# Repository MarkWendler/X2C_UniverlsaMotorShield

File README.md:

# X2C_Motorshield
Universal motor driver board for X2C Development board

## Planned Main features
* BLDC, PMSM motor drive
* 2 Phase Current sense
* 3 Phase voltage sense
* Led feedback from PWM outputs                                                                   
* Over current protection
* Optional Motor supply (Up to 48V Not)
* Interface to HALL sensor and Quadrature Encoder
* DC common current sens
* External OPAMP
* CAN Bus

## Recommended parts
* MOSFET:	DMT4002LPS			http://www.diodes.com/_files/datasheets/DMT4002LPS.pdf						
* Mosfet Driver:	MIC4607			http://www.microchip.com/wwwproducts/en/MIC4607						
* Current and voltage sense:	MCP6024 http://www.microchip.com/wwwproducts/en/MCP6024						
* 5V Supply LDO:	MCP1790/91									
* 8-12V LDO:	MIC5233 (Adjustable)			http://ww1.microchip.com/downloads/en/DeviceDoc/mic5233.pdf						
* CAN transciever:	ATA6563

### Pinout
Coming soon

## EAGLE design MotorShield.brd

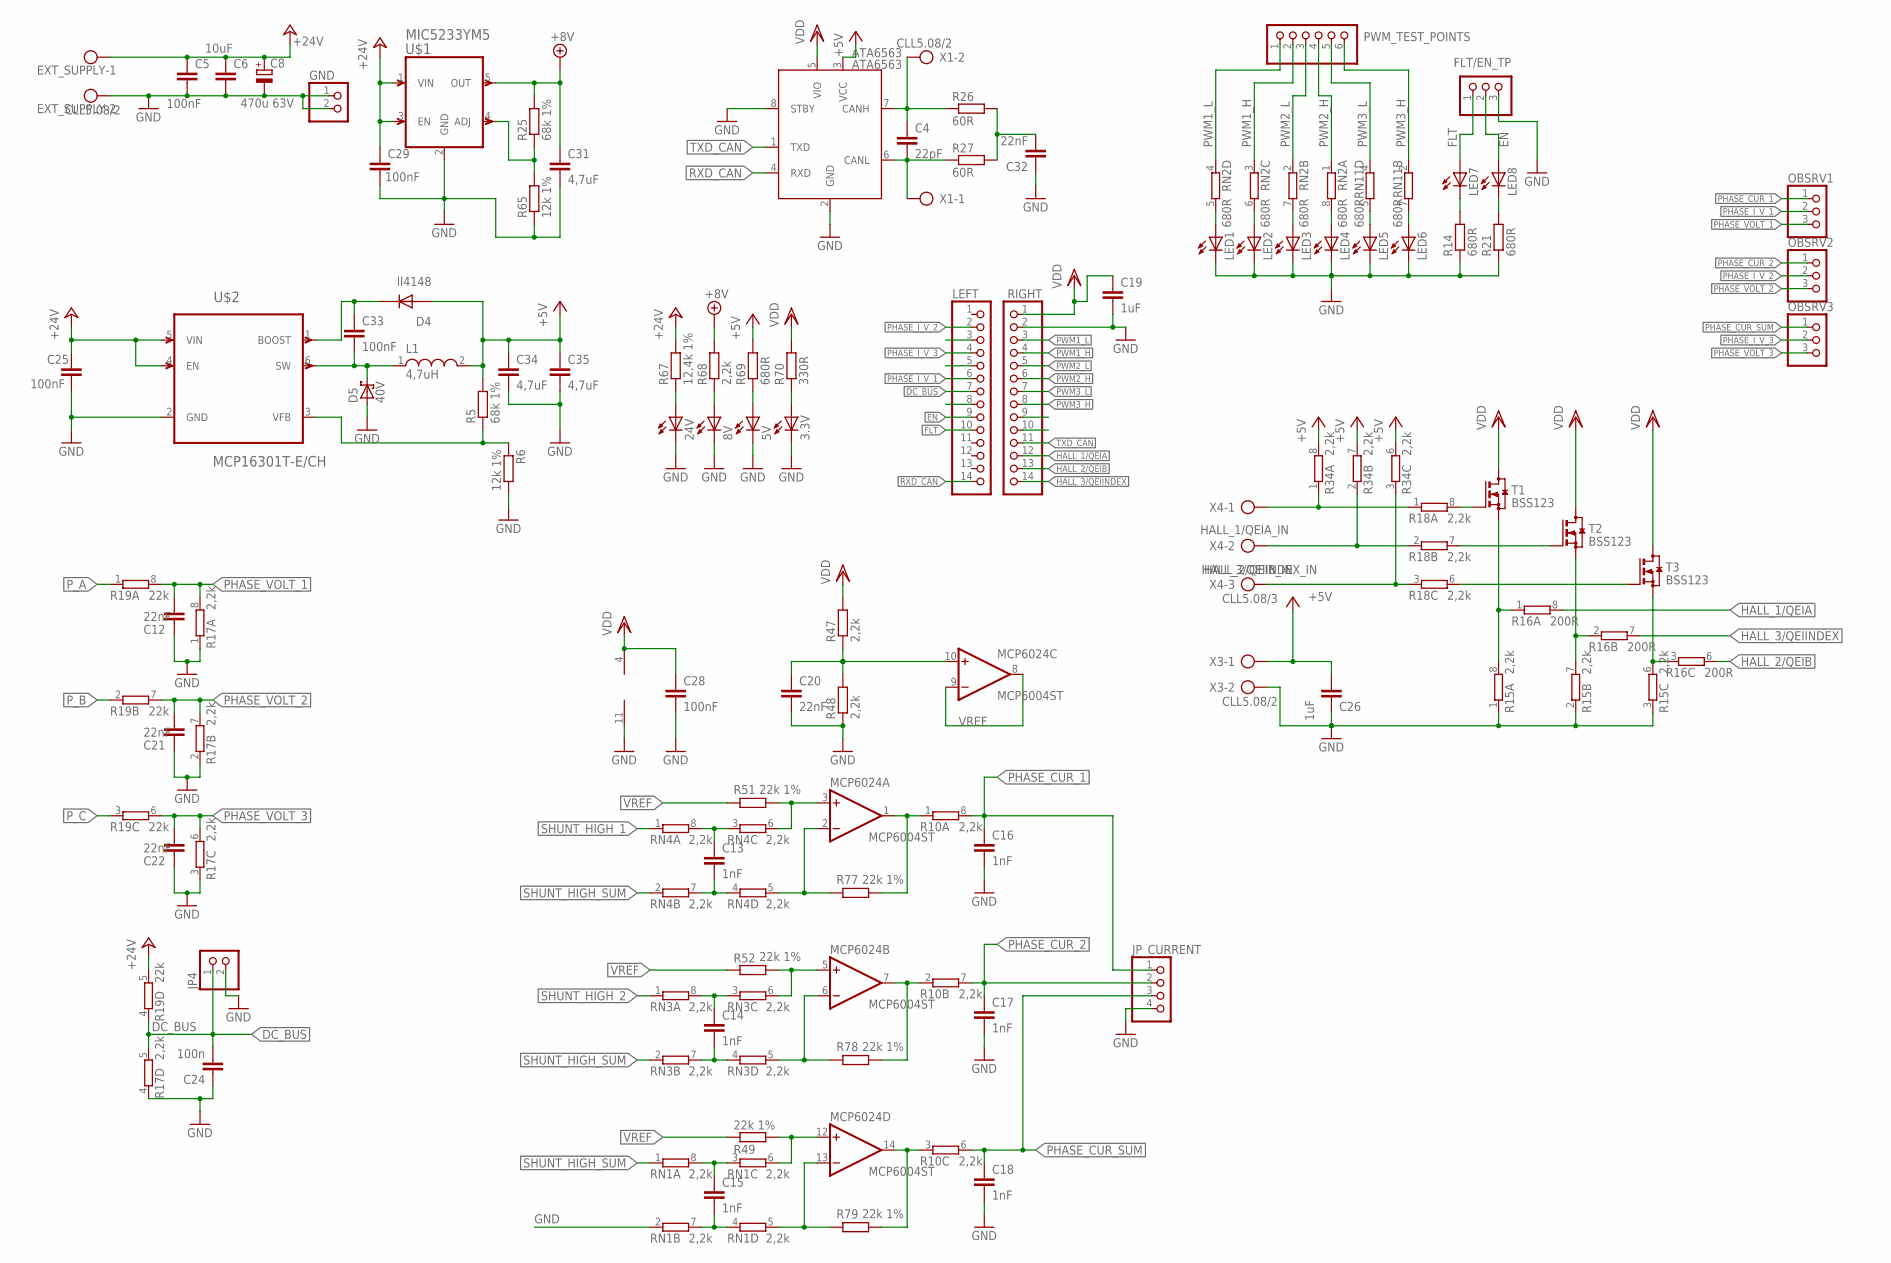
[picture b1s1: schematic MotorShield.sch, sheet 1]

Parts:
3.3V, 5V, 8V, 24V: Green; CHIPLED_0805
ATA6563: ATA6563; SOIC-8
C4: 22pF; C0603K
C5, C25, C28, C29, C33: 100nF; C0603K
C6: 10uF; C1206
C8: 470u 63V; PANASONIC_E
C12, C20, C21, C22, C32: 22nF; C0603K
C13, C14, C15, C16, C17, C18: 1nF; C0603K
C19, C26: 1uF; C0603K
C24: 100n; C0805
C31, C34, C35: 4,7uF; C0603K
D4: ll4148; MINIMELF
D5: 40V; MINIMELF
EXT_SUPPLY: CLL5.08/2
FLT/EN_TP: PINHD-1X3; 1X03
GND: PINHD-1X2; 1X02
JP4: PINHD-1X2; 1X02
JP_CURRENT: PINHD-1X4; 1X04
L1: 4,7uH; WE-TPC_3816
LED1, LED2, LED3, LED4, LED5, LED6: Yellow; CHIPLED_0805
LED7, LED8: Red; CHIPLED_0805
LEFT: PINHD-1X14; 1X14
MCP6024: MCP6004ST; TSSOP14
OBSRV1, OBSRV2, OBSRV3: PINHD-1X3; 1X03
PWM_TEST_POINTS: PINHD-1X6; 1X06
R5, R25: 68k 1%; R0603
R6, R65: 12k 1%; R0603
R10, R15, R17, R18, R34: 2,2k; EXBV8V_A
R14, R21, R69: 680R; R0603
R16: 200R; EXBV8V_A
R19: 22k; EXBV8V_A
R26, R27: 60R; R1206
R47, R48, R68: 2,2k; R0603
R49, R51, R52, R77, R78, R79: 22k 1%; R0603
R67: 12,4k 1%; R0603
R70: 330R; R0603
RIGHT: PINHD-1X14; 1X14
RN1, RN3, RN4: 2,2k; EXBV8V_A
RN2, RN11: 680R; EXBV8V_A
T1, T2, T3: BSS123; SOT23
U$1: MIC5233YM5; TSOT23-5
U$2: MCP16301T-E/CH; SOT23-6
X1, X3: CLL5.08/2
X4: CLL5.08/3

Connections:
+5V: ATA6563.3 (VCC), C26.1, C34.1, C35.1, D4.A, L1.2, R5.2, R34.6 (2), R34.7 (2), R34.8 (2), R69.2, X3.1
+8V: C31.1, R25.2, R68.2, U$1.5 (OUT); also elsewhere on the board
+24V: C5.1, C6.1, C8.+, C25.1, C29.1, EXT_SUPPLY.1, R19.5 (2), R67.2, U$1.1 (VIN), U$1.3 (EN), U$2.4 (EN), U$2.5 (VIN); also elsewhere on the board
CAN_H: ATA6563.7 (CANH), C4.1, R26.1, X1.2
CAN_L: ATA6563.6 (CANL), C4.2, R27.1, X1.1
DC_BUS: C24.2, JP4.1, LEFT.7, R17.5 (2), R19.4 (1)
EN: FLT/EN_TP.2, LED8.A, LEFT.9; also elsewhere on the board
FLT: FLT/EN_TP.1, LED7.A, LEFT.10; also elsewhere on the board
GND: 3.3V.C, 5V.C, 8V.C, 24V.C, ATA6563.2 (GND), ATA6563.8 (STBY), C5.2, C6.2, C8.-, C12.2, C16.2, C17.2, C18.2, C19.2, C20.2, C21.2, C22.2, C24.1, C25.2, C26.2, C28.2, C29.2, C31.2, C32.1, C34.2, C35.2, D5.A, EXT_SUPPLY.2, FLT/EN_TP.3, GND.1, GND.2, JP4.2, JP_CURRENT.4, LED1.C, LED2.C, LED3.C, LED4.C, LED5.C, LED6.C, MCP6024.11 (V-), R6.2, R14.1, R15.1, R15.2 (1), R15.3 (1), R17.1, R17.2 (1), R17.3 (1), R17.4 (1), R21.1, R48.1, R65.1, RIGHT.2, RN1.2 (1), U$1.2 (GND), U$2.2 (GND), X3.2; also elsewhere on the board
HALL_1/QEIA: R16.8 (2), RIGHT.12
HALL_1/QEIA_IN: R18.1, R34.1, X4.1
HALL_2/QEIB: R16.6 (2), RIGHT.13
HALL_2/QEIB_IN: R18.3 (1), R34.3 (1), X4.3
HALL_3/QEIINDEX: R16.7 (2), RIGHT.14
HALL_3/QEIINDEX_IN: R18.2 (1), R34.2 (1), X4.2
unnamed: MCP6024.3 (+IN), R51.2, RN4.6 (2)
unnamed: MCP6024.14 (OUT), R10.3 (1), R79.2
unnamed: MCP6024.7 (OUT), R10.2 (1), R78.2
unnamed: LED8.C, R21.2
unnamed: LED7.C, R14.2
unnamed: MCP6024.5 (+IN), R52.2, RN3.6 (2)
unnamed: C33.2, D5.C, L1.1, U$2.6 (SW)
unnamed: R25.1, R65.2, U$1.4 (ADJ)
unnamed: MCP6024.12 (+IN), R49.2, RN1.6 (2)
unnamed: R15.6 (2), R16.3 (1), T3.2 (S)
unnamed: R15.7 (2), R16.2 (1), T2.2 (S)
unnamed: R15.8 (2), R16.1, T1.2 (S)
unnamed: R18.8 (2), T1.1 (G)
unnamed: R18.7 (2), T2.1 (G)
unnamed: R18.6 (2), T3.1 (G)
unnamed: LED4.A, RN2.8 (2)
unnamed: LED3.A, RN2.7 (2)
unnamed: LED2.A, RN2.6 (2)
unnamed: 24V.A, R67.1
unnamed: 8V.A, R68.1
unnamed: 5V.A, R69.1
unnamed: 3.3V.A, R70.1
unnamed: C13.2, RN4.4 (1), RN4.7 (2)
unnamed: C13.1, RN4.3 (1), RN4.8 (2)
unnamed: MCP6024.2 (-IN), R77.1, RN4.5 (2)
unnamed: LED1.A, RN2.5 (2)
unnamed: C14.2, RN3.4 (1), RN3.7 (2)
unnamed: C14.1, RN3.3 (1), RN3.8 (2)
unnamed: LED5.A, RN11.5 (2)
unnamed: LED6.A, RN11.7 (2)
unnamed: R5.1, R6.1, U$2.3 (VFB)
unnamed: MCP6024.6 (-IN), R78.1, RN3.5 (2)
unnamed: C15.2, RN1.4 (1), RN1.7 (2)
unnamed: C15.1, RN1.3 (1), RN1.8 (2)
unnamed: MCP6024.13 (-IN), R79.1, RN1.5 (2)
unnamed: C33.1, D4.C, U$2.1 (BOOST)
unnamed: C32.2, R26.2, R27.2
unnamed: MCP6024.1 (OUT), R10.1, R77.2
unnamed: C20.1, MCP6024.10 (+IN), R47.1, R48.2
PHASE_CUR_1: C16.1, JP_CURRENT.1, OBSRV1.1, R10.8 (2)
PHASE_CUR_2: C17.1, JP_CURRENT.2, OBSRV2.1, R10.7 (2)
PHASE_CUR_SUM: C18.1, JP_CURRENT.3, OBSRV3.1, R10.6 (2)
PHASE_I_V_1: LEFT.6, OBSRV1.2
PHASE_I_V_2: LEFT.2, OBSRV2.2
PHASE_I_V_3: LEFT.4, OBSRV3.2
PHASE_VOLT_1: C12.1, OBSRV1.3, R17.8 (2), R19.8 (2)
PHASE_VOLT_2: C21.1, OBSRV2.3, R17.7 (2), R19.7 (2)
PHASE_VOLT_3: C22.1, OBSRV3.3, R17.6 (2), R19.6 (2)
PWM1_H: PWM_TEST_POINTS.2, RIGHT.4, RN2.3 (1); also elsewhere on the board
PWM1_L: PWM_TEST_POINTS.1, RIGHT.3, RN2.4 (1); also elsewhere on the board
PWM2_H: PWM_TEST_POINTS.4, RIGHT.6, RN2.1; also elsewhere on the board
PWM2_L: PWM_TEST_POINTS.3, RIGHT.5, RN2.2 (1); also elsewhere on the board
PWM3_H: PWM_TEST_POINTS.6, RIGHT.8, RN11.2 (1); also elsewhere on the board
PWM3_L: PWM_TEST_POINTS.5, RIGHT.7, RN11.4 (1); also elsewhere on the board
P_A: R19.1; also elsewhere on the board
P_B: R19.2 (1); also elsewhere on the board
P_C: R19.3 (1); also elsewhere on the board
RXD_CAN: ATA6563.4 (RXD), LEFT.14
SHUNT_HIGH_1: RN4.1; also elsewhere on the board
SHUNT_HIGH_2: RN3.1; also elsewhere on the board
SHUNT_HIGH_SUM: RN1.1, RN3.2 (1), RN4.2 (1); also elsewhere on the board
TXD_CAN: ATA6563.1 (TXD), RIGHT.11
VDD: ATA6563.5 (VIO), C19.1, C28.1, MCP6024.4 (V+), R47.2, R70.2, RIGHT.1, T1.3 (D), T2.3 (D), T3.3 (D); also elsewhere on the board
VREF: MCP6024.8 (OUT), MCP6024.9 (-IN), R49.1, R51.1, R52.1

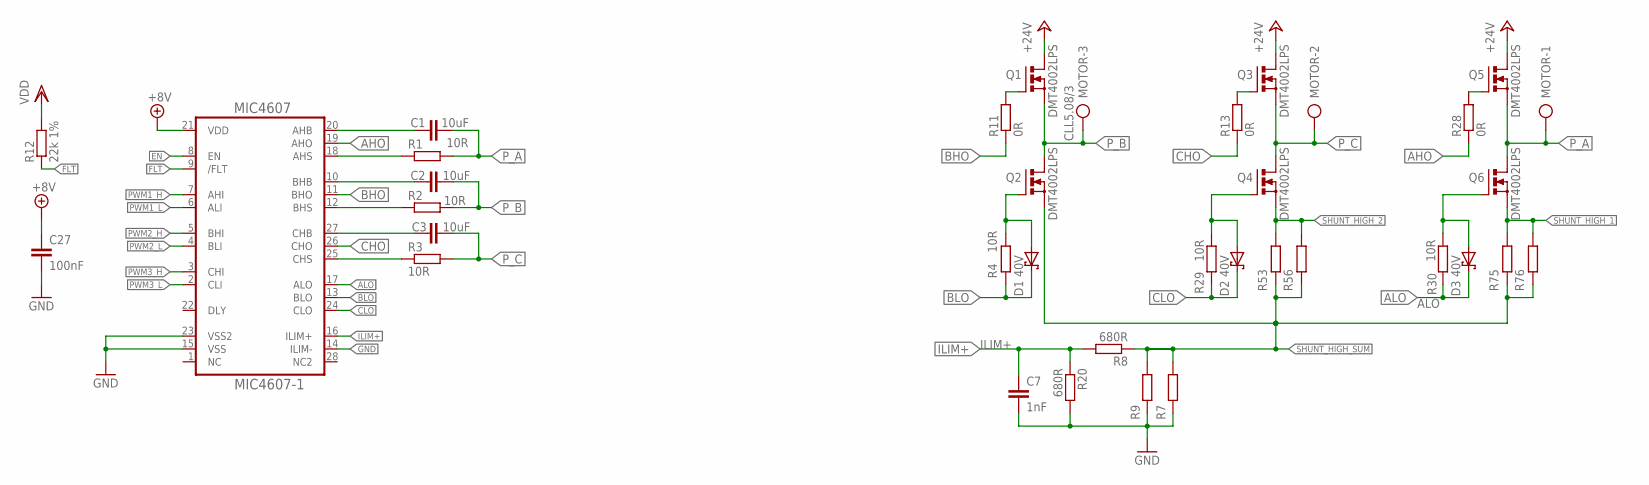
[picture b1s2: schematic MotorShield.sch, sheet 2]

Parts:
C1, C2, C3: 10uF; C0805K
C7: 1nF; C0603K
C27: 100nF; C0603K
D1, D2, D3: 40V; MINIMELF
MIC4607: MIC4607-1; TSSOP28
MOTOR: CLL5.08/3
Q1, Q2, Q3, Q4, Q5, Q6: DMT4002LPS; PG-TDSON-8_
R1, R2, R3, R4, R29, R30: 10R; R0603
R7, R9, R53, R56, R75, R76: R-EU_SMDR2512; R2512
R8, R20: 680R; R0603
R11, R13, R28: 0R; R0603
R12: 22k 1%; R0603

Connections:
+8V: C27.1, MIC4607.21 (VDD); also elsewhere on the board
+24V: Q1.5 (D), Q1.6 (D), Q1.7 (D), Q1.8 (D), Q1.TH (D), Q3.5 (D), Q3.6 (D), Q3.7 (D), Q3.8 (D), Q3.TH (D), Q5.5 (D), Q5.6 (D), Q5.7 (D), Q5.8 (D), Q5.TH (D); also elsewhere on the board
AHB: C1.1, MIC4607.20 (AHB)
AHO: MIC4607.19 (AHO), R28.1
AHS: MIC4607.18 (AHS), R1.1
ALO: D3.C, MIC4607.17 (ALO), R30.2
BHB: C2.1, MIC4607.10 (BHB)
BHO: MIC4607.11 (BHO), R11.1
BHS: MIC4607.12 (BHS), R2.1
BLO: D1.C, MIC4607.13 (BLO), R4.1
CHB: C3.1, MIC4607.27 (CHB)
CHO: MIC4607.26 (CHO), R13.1
CHS: MIC4607.25 (CHS), R3.1
CLO: D2.C, MIC4607.24 (CLO), R29.2
EN: MIC4607.8 (EN); also elsewhere on the board
FLT: MIC4607.9 (/FLT), R12.1; also elsewhere on the board
GND: C7.2, C27.2, MIC4607.14 (ILIM-), MIC4607.15 (VSS), MIC4607.23 (VSS2), R7.1, R9.1, R20.2; also elsewhere on the board
ILIM+: C7.1, MIC4607.16 (ILIM+), R8.2, R20.1
unnamed: Q1.4 (G), R11.2
unnamed: Q3.4 (G), R13.2
unnamed: Q5.4 (G), R28.2
unnamed: D1.A, Q2.4 (G), R4.2
unnamed: D2.A, Q4.4 (G), R29.1
unnamed: D3.A, Q6.4 (G), R30.1
PWM1_H: MIC4607.7 (AHI); also elsewhere on the board
PWM1_L: MIC4607.6 (ALI); also elsewhere on the board
PWM2_H: MIC4607.5 (BHI); also elsewhere on the board
PWM2_L: MIC4607.4 (BLI); also elsewhere on the board
PWM3_H: MIC4607.3 (CHI); also elsewhere on the board
PWM3_L: MIC4607.2 (CLI); also elsewhere on the board
P_A: C1.2, MOTOR.1, Q5.1 (S), Q5.2 (S), Q5.3 (S), Q6.5 (D), Q6.6 (D), Q6.7 (D), Q6.8 (D), Q6.TH (D), R1.2; also elsewhere on the board
P_B: C2.2, MOTOR.3, Q1.1 (S), Q1.2 (S), Q1.3 (S), Q2.5 (D), Q2.6 (D), Q2.7 (D), Q2.8 (D), Q2.TH (D), R2.2; also elsewhere on the board
P_C: C3.2, MOTOR.2, Q3.1 (S), Q3.2 (S), Q3.3 (S), Q4.5 (D), Q4.6 (D), Q4.7 (D), Q4.8 (D), Q4.TH (D), R3.2; also elsewhere on the board
SHUNT_HIGH_1: Q6.1 (S), Q6.2 (S), Q6.3 (S), R75.2, R76.2; also elsewhere on the board
SHUNT_HIGH_2: Q4.1 (S), Q4.2 (S), Q4.3 (S), R53.2, R56.2; also elsewhere on the board
SHUNT_HIGH_SUM: Q2.1 (S), Q2.2 (S), Q2.3 (S), R7.2, R8.1, R9.2, R53.1, R56.1, R75.1, R76.1; also elsewhere on the board
VDD: R12.2; also elsewhere on the board

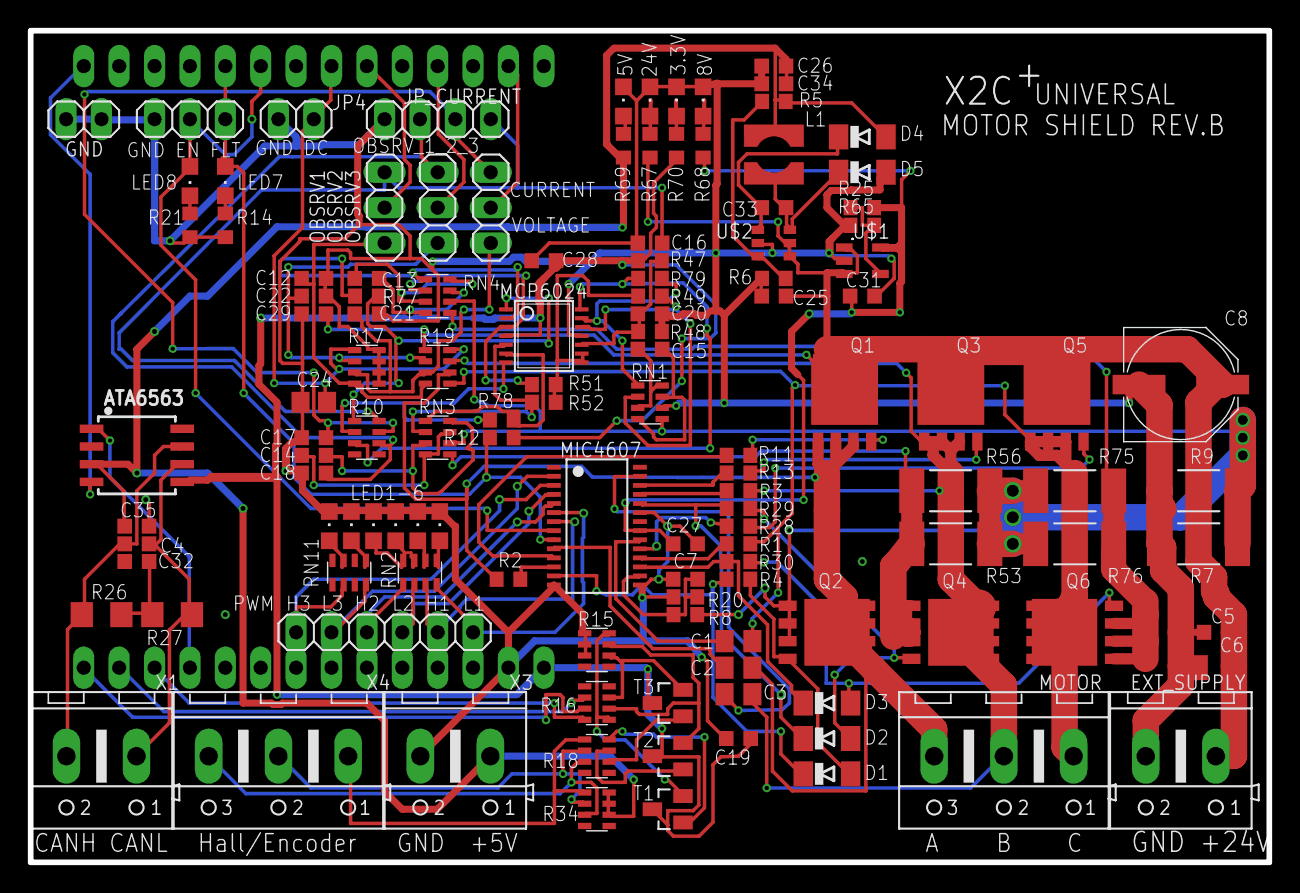
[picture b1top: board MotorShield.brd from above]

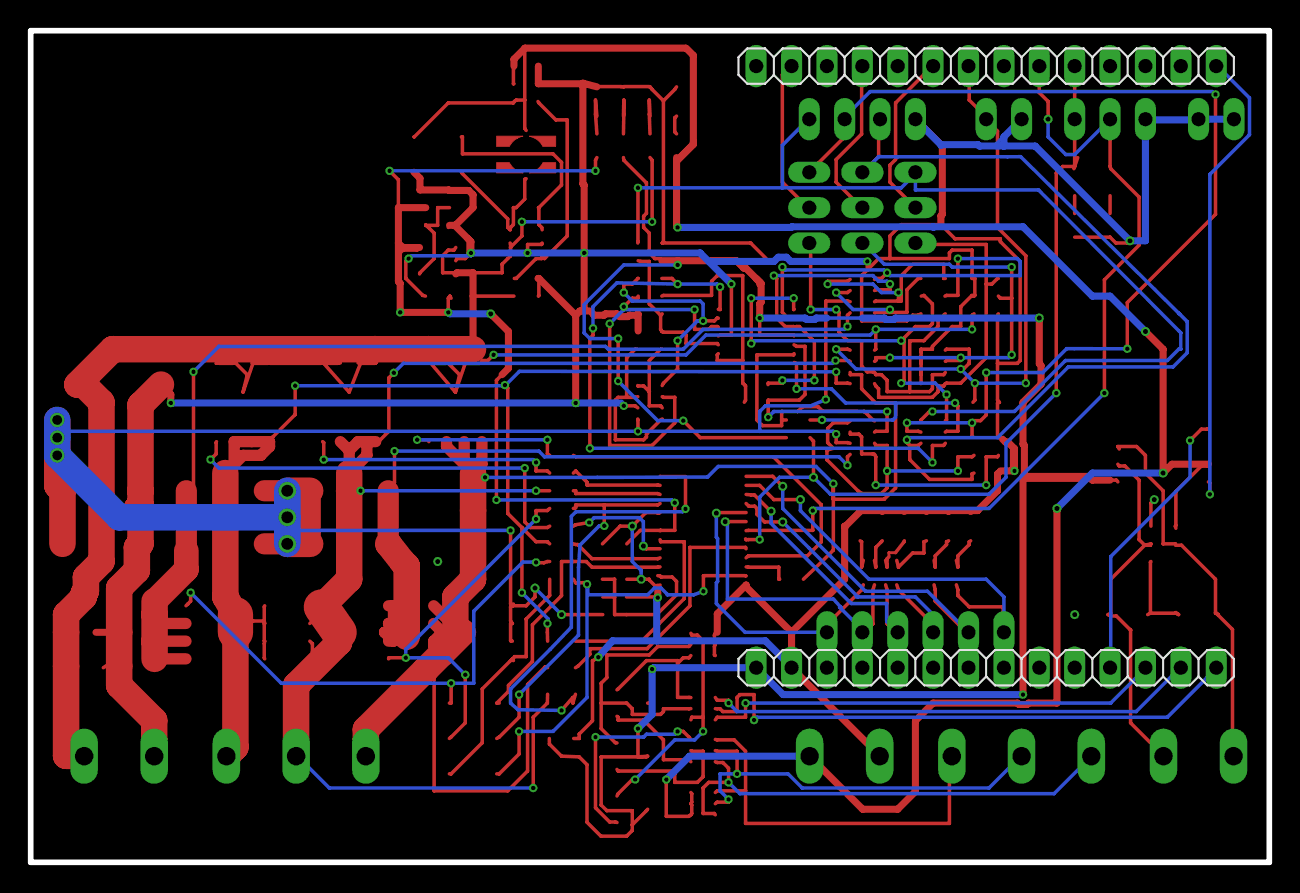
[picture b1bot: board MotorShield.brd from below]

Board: 2 copper layers, 88.9 x 59.7 mm, 127 parts (2 on the bottom side), 98 nets.

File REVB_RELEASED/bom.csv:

"Qty";"Value";"Device";"Package";"Parts";"Description";"EAGLEID";"MCHP_ID";"MF";"MPN";"OC_FARNELL";"OC_NEWARK";"SPICEPREFIX";"TME";"VALUE";
"2";"";"PINHD-1X14";"1X14";"LEFT, RIGHT";"PIN HEADER";"";"";"";"";"";"";"";"";"";
"2";"";"PINHD-1X2";"1X02";"GND, JP4";"PIN HEADER";"";"";"";"";"";"";"";"";"";
"4";"";"PINHD-1X3";"1X03";"FLT/EN_TP, OBSRV1, OBSRV2, OBSRV3";"PIN HEADER";"";"";"";"";"";"";"";"";"";
"1";"";"PINHD-1X4";"1X04";"JP_CURRENT";"PIN HEADER";"";"";"";"";"";"";"";"";"";
"1";"";"PINHD-1X6";"1X06";"PWM_TEST_POINTS";"PIN HEADER";"";"";"";"";"";"";"";"";"";
"3";"0R";"R-EU_SMDR0603_0R";"R0603";"R11, R13, R28";"RESISTOR, European symbol";"";"";"";"";"";"";"";"";"0R";
"1";"100n";"C-EUC0805";"C0805";"C24";"CAPACITOR, European symbol";"";"";"";"";"";"";"C";"";"";
"6";"100nF";"C-EU-SMD_0603_100NF_50V";"C0603K";"C5, C25, C27, C28, C29, C33";"CAPACITOR, European symbol";"1204";"";"";"";"";"";"";"";"100nF";
"3";"10uF";"C-EU-SMD_0805_10UF_16V";"C0805K";"C1, C2, C3";"CAPACITOR, European symbol";"1275";"";"";"";"";"";"";"";"10uF";
"1";"10uF";"C-EU-SMD_1206_10UF_50V";"C1206";"C6";"CAPACITOR, European symbol";"1368";"";"";"";"";"";"";"";"10uF";
"1";"12,4k 1%";"R-EU_SMDR0603_12,4K_1%";"R0603";"R67";"RESISTOR, European symbol";"1316";"";"";"";"";"";"";"";"12,4k 1%";
"2";"12k 1%";"R-EU_SMDR0603_12K_1%";"R0603";"R6, R65";"RESISTOR, European symbol";"1317";"";"";"";"";"";"";"";"12k 1%";
"2";"1k";"4R-NEXB38V";"EXB38V";"RN2, RN11";"Array Chip Resistor";"";"";"";"";"unknown";"unknown";"";"";"";
"7";"1nF";"C-EU-SMD_0603_1NF_100V";"C0603K";"C7, C13, C14, C15, C16, C17, C18";"CAPACITOR, European symbol";"";"";"";"";"";"";"";"";"1nF";
"2";"1uF";"C-EU-SMD_0603_1UF_10V";"C0603K";"C19, C26";"CAPACITOR, European symbol";"1309";"";"";"";"";"";"";"";"1uF";
"8";"2,2k";"4R-N2,2K";"EXBV8V_A";"R10, R15, R17, R18, R34, RN1, RN3, RN4";"Array Chip Resistor";"1022";"";"";"";"";"";"";"";"2,2k";
"3";"2,2k";"R-EU_SMDR0603_2,2K";"R0603";"R47, R48, R68";"RESISTOR, European symbol";"1364";"";"";"";"";"";"";"";"2,2k";
"1";"200R";"4R-N200R";"EXBV8V_A";"R16";"Array Chip Resistor";"1023";"";"";"";"";"";"";"";"200R";
"1";"22k";"4R-N22K";"EXBV8V_A";"R19";"Array Chip Resistor";"";"";"";"";"";"";"";"";"22k";
"7";"22k 1%";"R-EU_SMDR0603_22K_1%";"R0603";"R12, R49, R51, R52, R77, R78, R79";"RESISTOR, European symbol";"1314";"";"";"";"";"";"";"";"22k 1%";
"5";"22nF";"C-EU-SMD_0603_22NF_16V";"C0603K";"C12, C20, C21, C22, C32";"CAPACITOR, European symbol";"1311";"";"";"";"";"";"";"";"22nF";
"1";"22pF";"C-EU-SMD_0603_22PF_50V";"C0603K";"C4";"CAPACITOR, European symbol";"1312";"";"";"";"";"";"";"";"22pF";
"1";"330R";"R-EU_SMDR0603_330R";"R0603";"R70";"RESISTOR, European symbol";"1374";"";"";"";"";"";"";"";"330R";
"6";"3R";"R-EU_SMDR0603_3R";"R0603";"R1, R2, R3, R4, R29, R30";"RESISTOR, European symbol";"";"";"";"";"";"";"";"";"3R";
"3";"4,7uF";"C-EU-SMD_0603_4,7UF_16V";"C0603K";"C31, C34, C35";"CAPACITOR, European symbol";"1310";"";"";"";"";"";"";"";"4,7uF";
"1";"4,7uH";"WE-TPC_3816_4,7UH_0,9A";"WE-TPC_3816";"L1";"SMD Shielded Tiny Power Inductor";"";"";"";"";"";"";"";"";"4,7uH";
"4";"40V";"SCHOTTKY40V";"MINIMELF";"D1, D2, D3, D5";"Schottky Diode";"";"";"";"";"";"";"";"TMMBAT48FILM";"40V";
"1";"470u 63V";"CPOL-EUE";"PANASONIC_E";"C8";"POLARIZED CAPACITOR, European symbol";"";"";"";"";"";"";"C";"";"";
"2";"60R";"R-EU_SMDR1206_60R";"R1206";"R26, R27";"RESISTOR, European symbol";"";"";"";"";"";"";"";"";"60R";
"5";"680R";"R-EU_SMDR0603_680R";"R0603";"R8, R14, R20, R21, R69";"RESISTOR, European symbol";"";"";"";"";"";"";"";"";"680R";
"2";"68k 1%";"R-EU_SMDR0603_68K_1%";"R0603";"R5, R25";"RESISTOR, European symbol";"1324";"";"";"";"";"";"";"";"68k 1%";
"1";"ATA6563";"ATA6563";"SOIC-8";"ATA6563";"";"";"";"";"";"";"";"";"";"ATA6563";
"3";"BSS123";"BSS123";"SOT23";"T1, T2, T3";"N-CHANNEL MOS FET";"1139";"";"";"";"";"";"";"";"BSS123";
"3";"CLL5.08/2";"AK500/2CSAVAROS_CLL5.08/2";"CLL5.08/2";"EXT_SUPPLY, X1, X3";"CONNECTOR";"1029";"";"";"";"";"";"";"";"CLL5.08/2";
"2";"CLL5.08/3";"AK500/3CSAVAROS_CLL5.08/3";"CLL5.08/3";"MOTOR, X4";"CONNECTOR";"1030";"";"";"";"";"";"";"";"CLL5.08/3";
"6";"DMT4002LPS";"BSZ105N04NS_PG-TDSON-8";"PG-TDSON-8_";"Q1, Q2, Q3, Q4, Q5, Q6";"OptiMOS (TM)3 Power-Transistor N-Channel, Normal level";"";"";"";"";"";"";"";"";"";
"4";"Green";"LEDCHIPLED_0805_GREEN";"CHIPLED_0805";"3.3V, 5V, 8V, 24V";"LED";"1109";"";"";"";"";"";"";"";"Green";
"1";"MCP16301T-E/CH";"MCP16301T-E/CH";"SOT23-6";"U$2";"Microchip Buck regulator MCP16301";"";"MIC19965";"";"";"";"";"";"";"";
"1";"MCP6004ST";"MCP6004ST";"TSSOP14";"MCP6024";"Quad Op Amp 2.7V to 6.0V Single Supply";"";"";"";"";"";"";"";"";"";
"1";"MIC4607-1";"MIC4607-1";"TSSOP28";"MIC4607";"Microchip MIC4607 Datasheet";"";"";"";"";"";"";"";"";"";
"1";"MIC5233YM5";"MIC5233YM5";"TSOT23-5";"U$1";"Microchip MIC5233";"";"";"";"";"";"";"";"";"";
"6";"R-EU_SMDR2512";"R-EU_SMDR2512";"R2512";"R7, R9, R53, R56, R75, R76";"RESISTOR, European symbol";"";"";"";"";"";"";"";"";"";
"2";"Red";"LEDCHIPLED_0805_RED";"CHIPLED_0805";"LED7, LED8";"LED";"1110";"";"";"";"";"";"";"";"Red";
"6";"Yellow";"LEDCHIPLED_0805_YELLOW";"CHIPLED_0805";"LED1, LED2, LED3, LED4, LED5, LED6";"LED";"1112";"";"";"";"";"";"";"";"Yellow";
"1";"ll4148";"1N4148MINIMELF";"MINIMELF";"D4";"DIODE";"1075";"";"";"";"";"";"";"DL4148";"ll4148";

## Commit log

2017-11-29 Basic updates in the readme
2017-11-29 Added Daniel's changes Fixed Mosfet Driver IC pinout Modified HALL/QIE connection And some other changes
2017-12-07 first version of docs/user_guide.docx
2018-01-16 Newest docs added
2018-02-13 Kando library added
2018-08-03 REVB version update
2018-08-03 MPLAB project added
